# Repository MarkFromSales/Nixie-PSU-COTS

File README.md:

# Nixie-PSU-COTS
Power supply for microcontroller + Nixue tubes using Common Off The Shelf components

This will eventually be replaced by my own hand-built supply. Another in a sea of them, but this is more about my learning than building a product.

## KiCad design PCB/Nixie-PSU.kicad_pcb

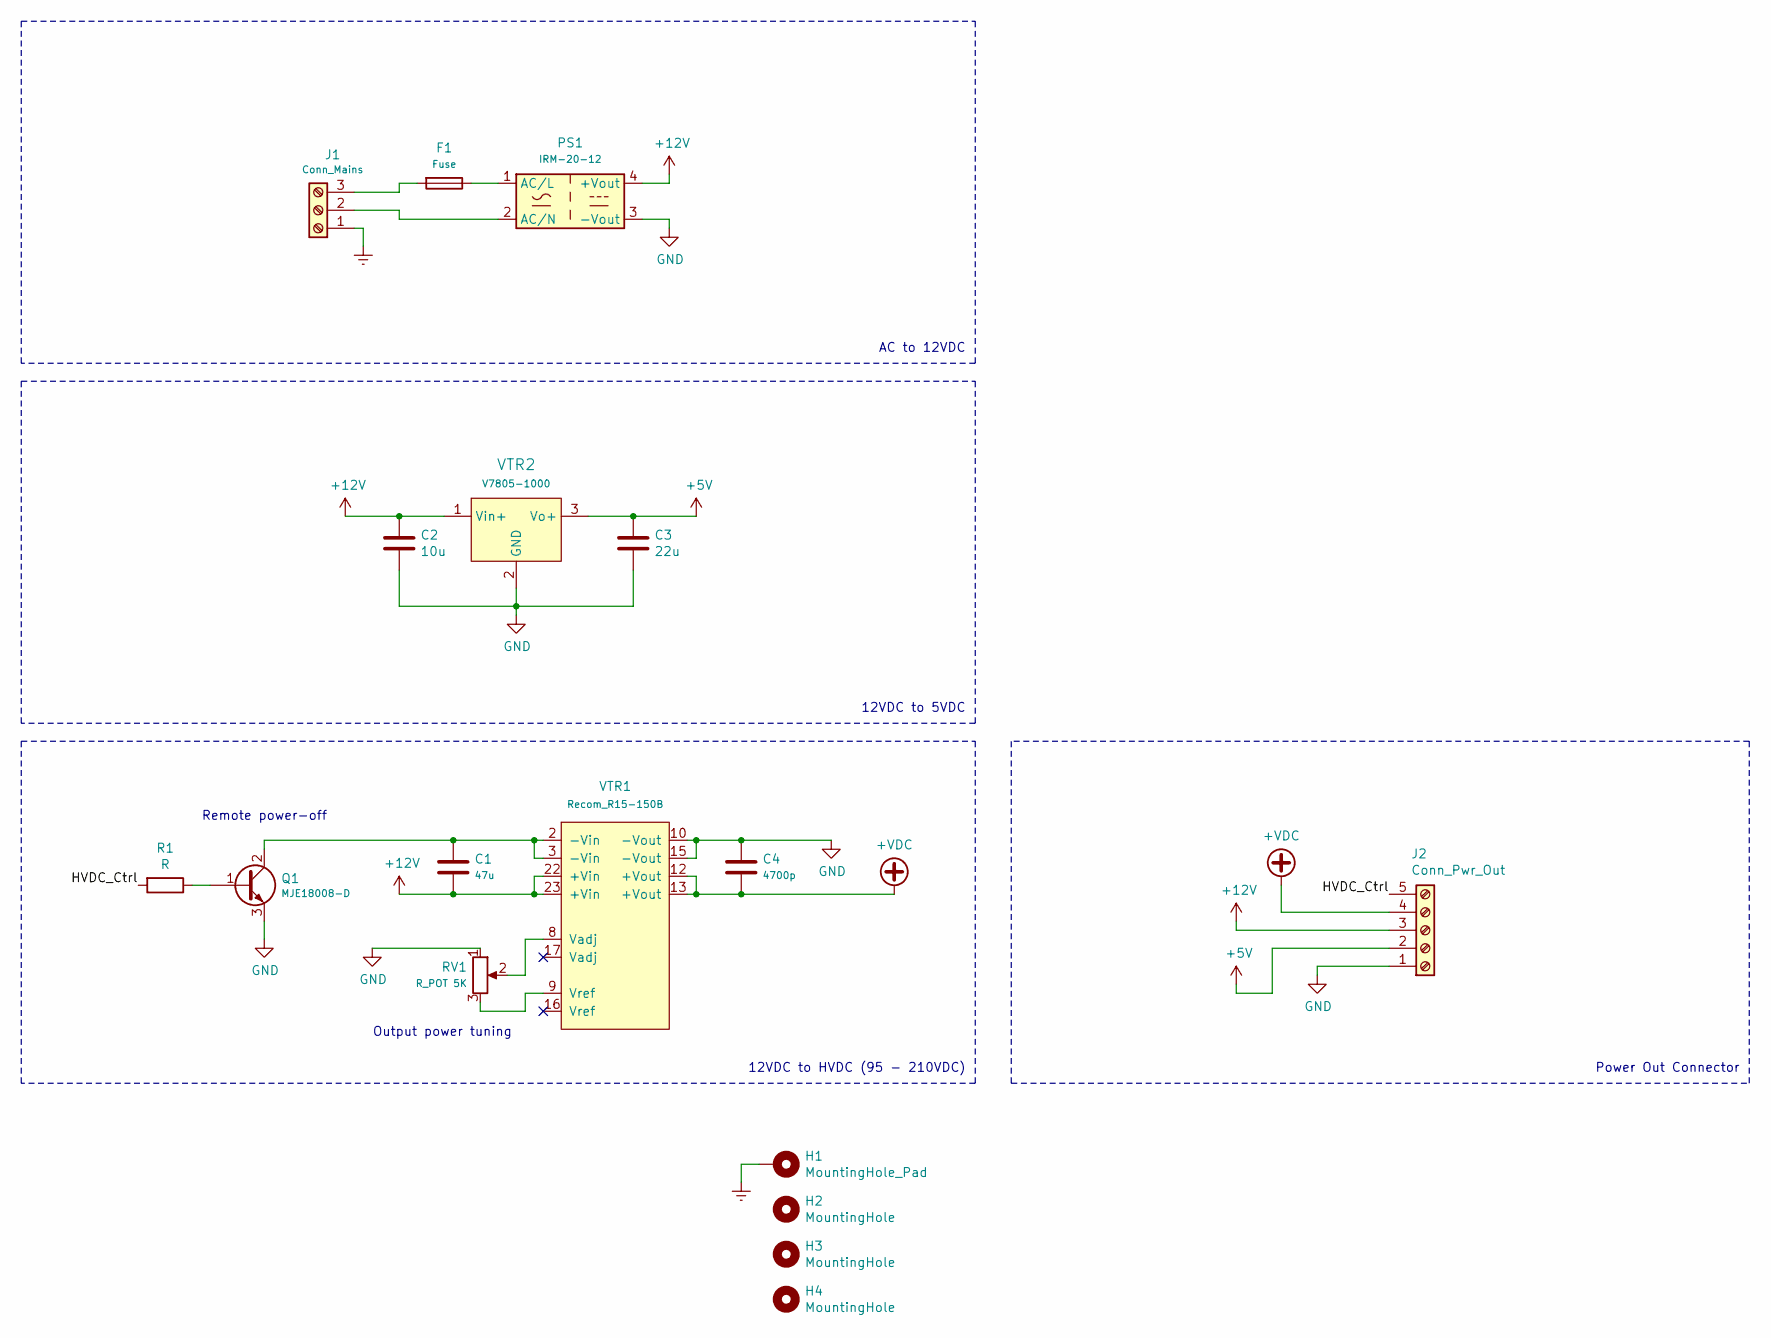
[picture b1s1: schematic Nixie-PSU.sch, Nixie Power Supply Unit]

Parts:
C1: 47u; C_1210_3225Metric_Pad1.42x2.65mm_HandSolder
C2: 10u; C_0805_2012Metric_Pad1.15x1.40mm_HandSolder
C3: 22u; C_0805_2012Metric_Pad1.15x1.40mm_HandSolder
C4: 4700p; C_0805_2012Metric_Pad1.15x1.40mm_HandSolder
F1: Fuse; Fuseholder_TR5_Littelfuse_No560_No460
H1: MountingHole_Pad; MountingHole_3mm_Pad
H2, H3, H4: MountingHole; MountingHole_3.2mm_M3
J1: Conn_Mains; JST_VH_B3P-VH_1x03_P3.96mm_Vertical
J2: Conn_Pwr_Out; TerminalBlock_TE_282834-5_1x05_P2.54mm_Horizontal
PS1: IRM-20-12; Converter_ACDC_MeanWell_IRM-20-xx_THT
Q1: MJE18008-D; TO-220F-3_Vertical
R1: R; R_0805_2012Metric_Pad1.15x1.40mm_HandSolder
RV1: R_POT 5K; Potentiometer_Vishay_43_Horizontal
VTR1: Recom_R15-150B; DIP-24_W15.24mm
VTR2: V7805-1000; 3-SIP_Module_V7805-1000; MPN V7805-1000; Digi-Key_PN 102-1715-ND

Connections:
+5V: C3.1, J2.2, VTR2.3 (Vo+)
+12V: C1.2, C2.1, J2.3, PS1.4 (+Vout), VTR1.22 (+Vin), VTR1.23 (+Vin), VTR2.1 (Vin+)
+VDC: C4.2, J2.4, VTR1.12 (+Vout), VTR1.13 (+Vout)
/HVDC_Ctrl: J2.5, R1.2
Earth: H1.1, J1.1
GND: C2.2, C3.2, C4.1, J2.1, PS1.3 (-Vout), Q1.3 (E), RV1.1, VTR1.10 (-Vout), VTR1.15 (-Vout), VTR2.2 (GND)
unnamed: C1.1, Q1.2 (C), VTR1.2 (-Vin), VTR1.3 (-Vin)
unnamed: F1.1, PS1.1 (AC/L)
unnamed: F1.2, J1.3
unnamed: J1.2, PS1.2 (AC/N)
unnamed: Q1.1 (B), R1.1
unnamed: RV1.2, VTR1.8 (Vadj)
unnamed: RV1.3, VTR1.9 (Vref)

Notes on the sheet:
AC to 12VDC
12VDC to 5VDC
12VDC to HVDC (95 - 210VDC)
Remote power-off
Output power tuning
Power Out Connector

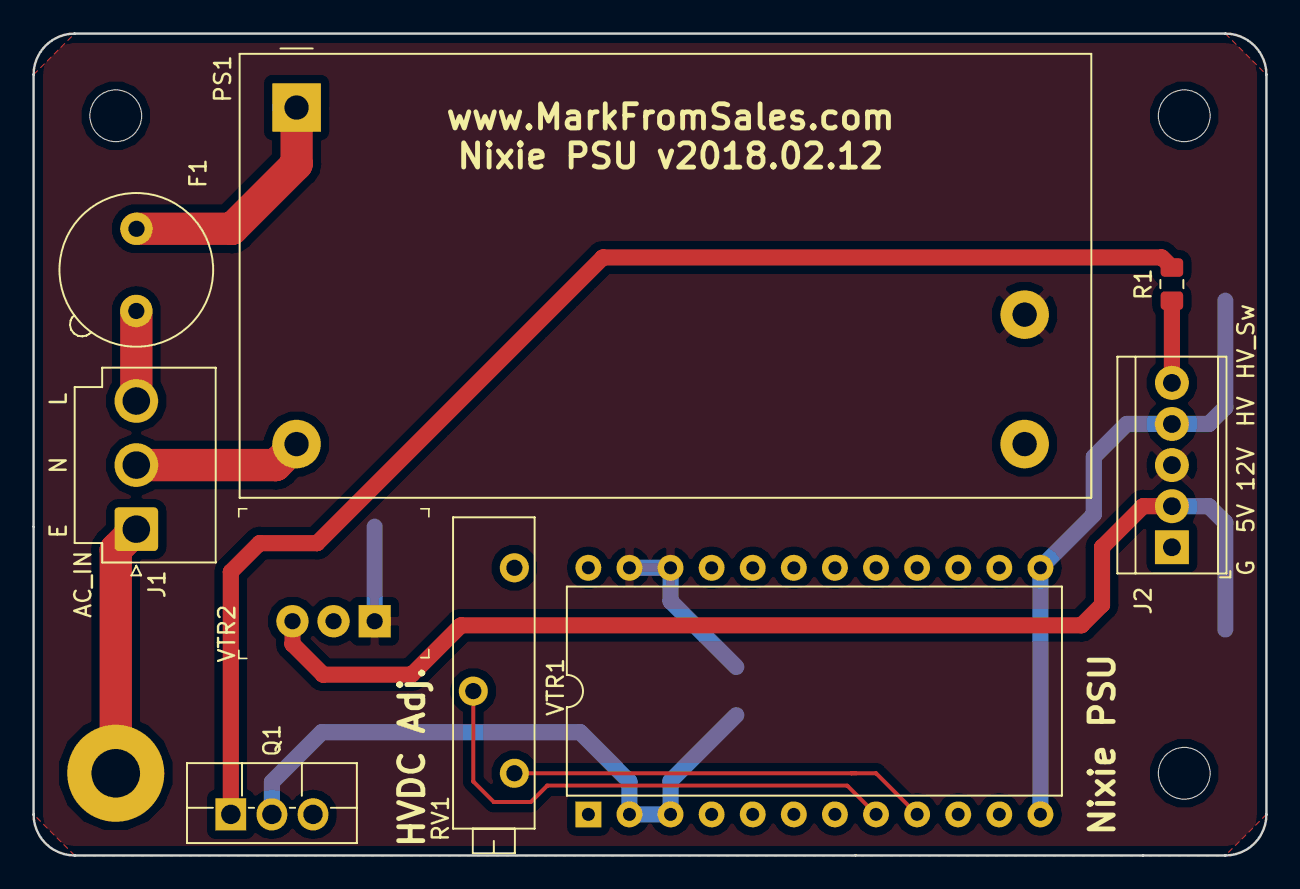
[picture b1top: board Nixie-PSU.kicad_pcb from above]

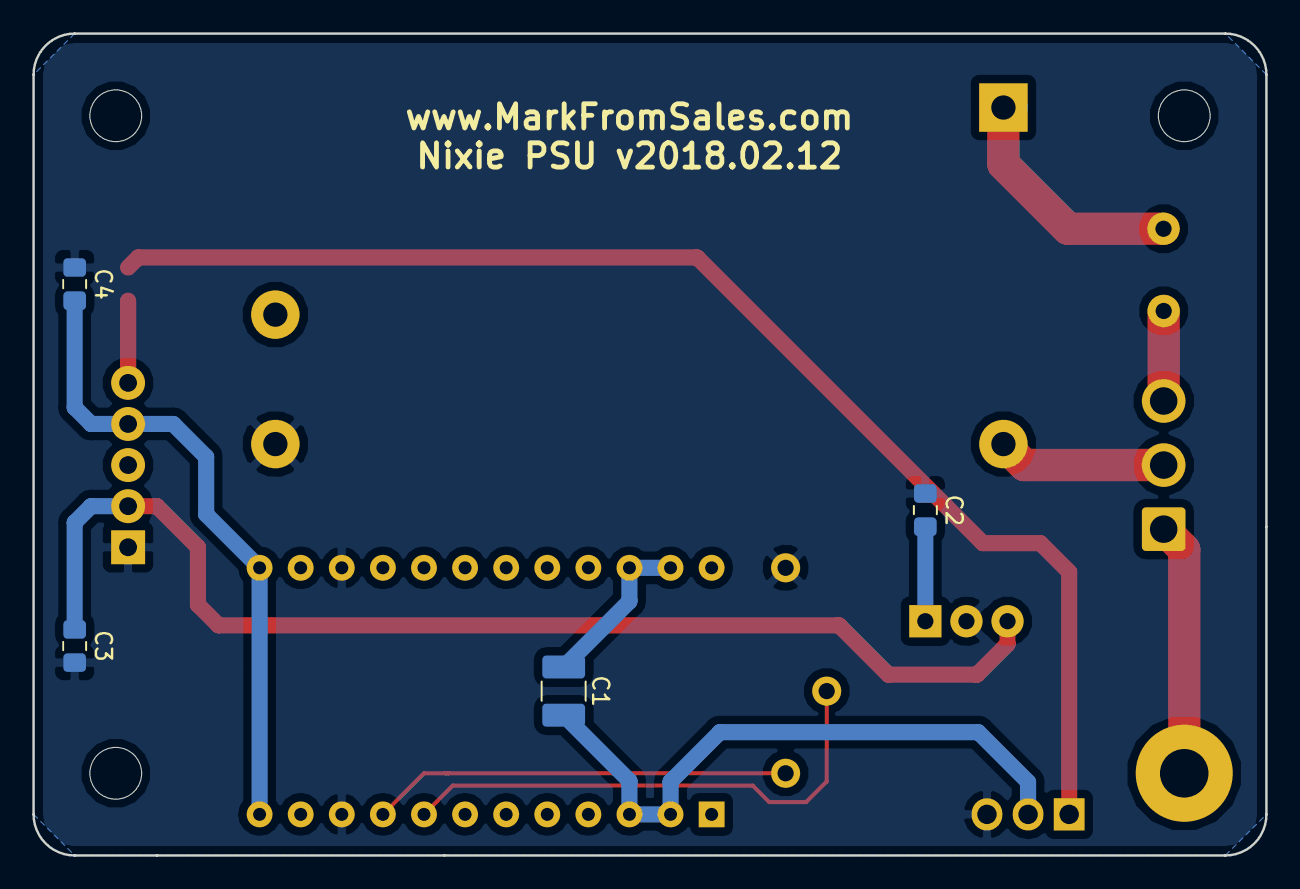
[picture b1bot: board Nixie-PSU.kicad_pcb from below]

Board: 2 copper layers, 76.2 x 50.8 mm, 17 parts (4 on the bottom side), 13 nets.

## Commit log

2019-02-02 Initial Upload
2019-02-03 Cleaned-up docs slightly
2019-02-13 Updated structure
2019-02-13 Rounded Corners
